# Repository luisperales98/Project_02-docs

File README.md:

# Project_02-docs
PCB design for Golf Ball Dispenser

I apologize for the messiness of the depository... At first I was not able to make subfolders, but then I did it but was not
able to delete the files already uploaded.

This repository shows the PCB design for my Golf Ball Dispenser Project. 
The general function for this device is that it dispenses a golf ball using a Servo motor when motion is detected from the PIR sensor and at the same time plays a little jingle as well. For more information, go to my hackster page below:
https://www.hackster.io/luis-perales/golf-ball-dispenser-301dcc

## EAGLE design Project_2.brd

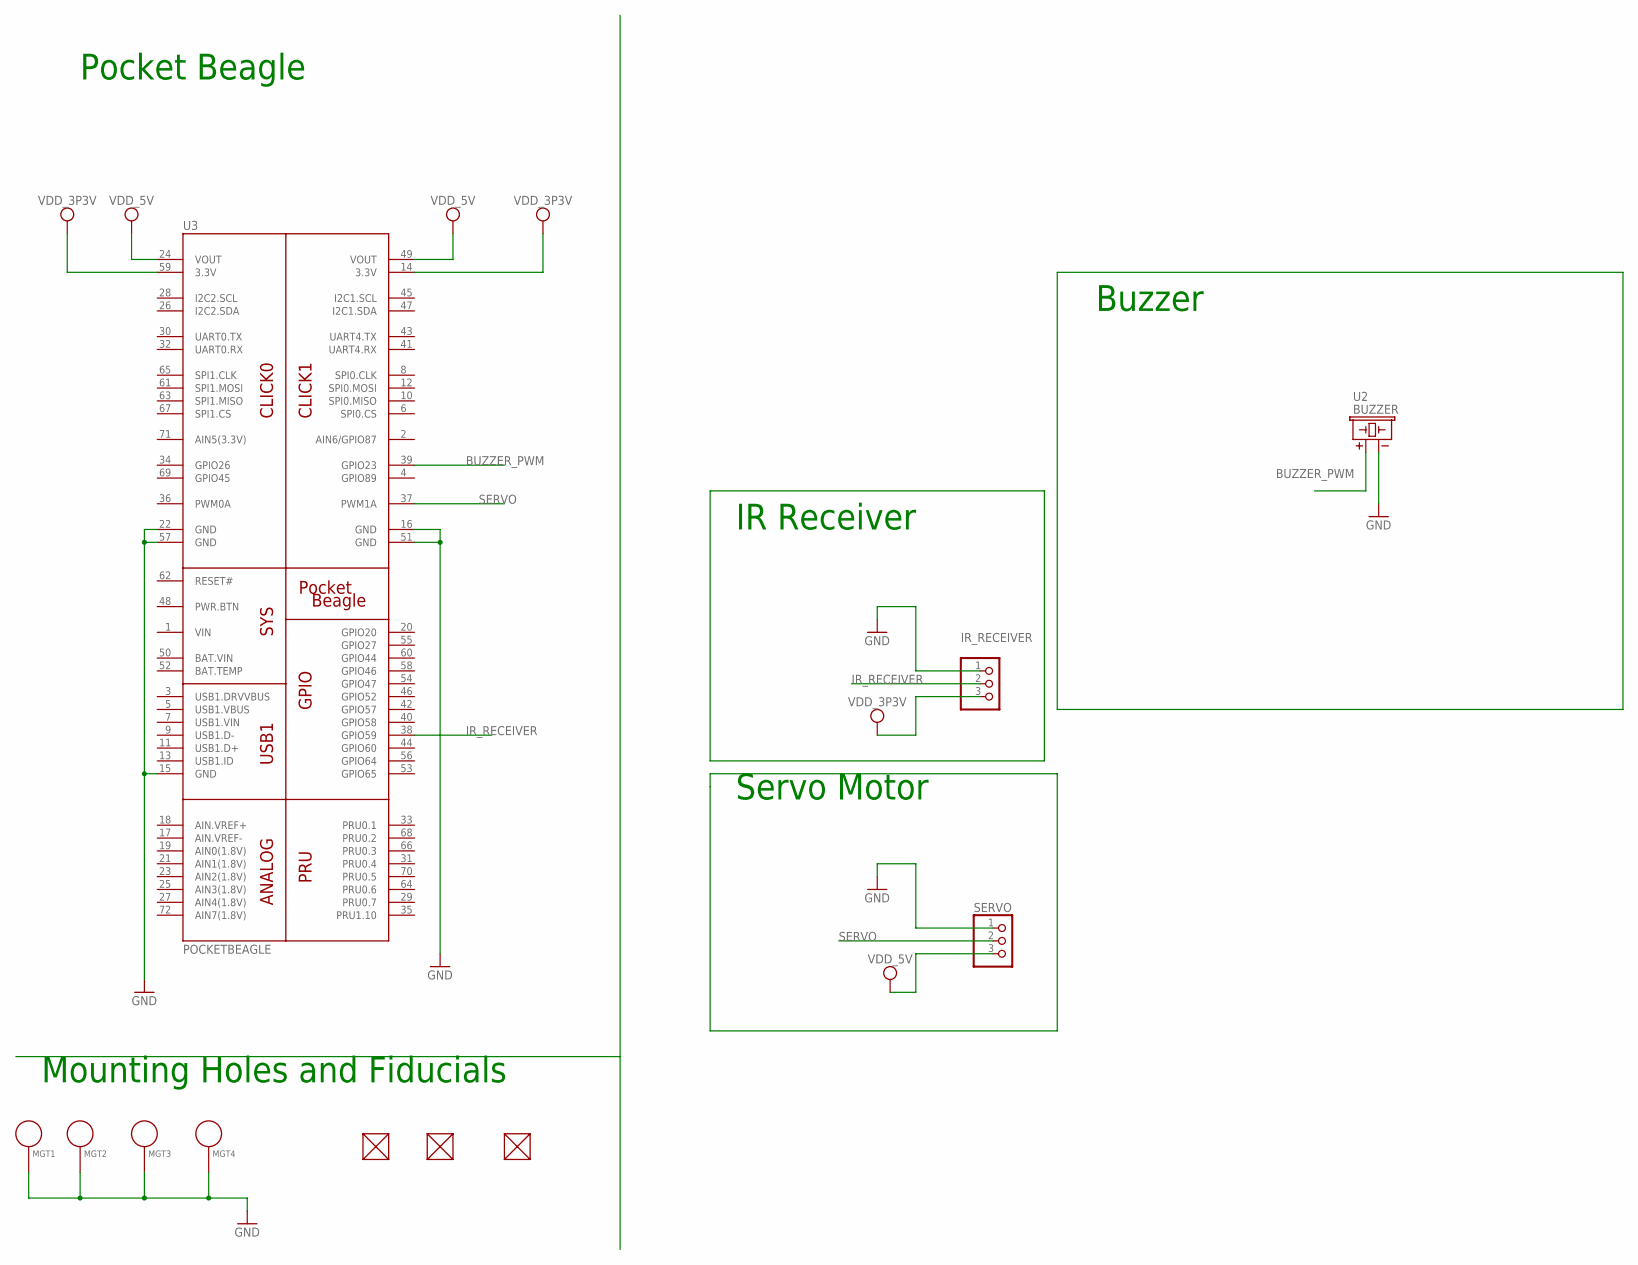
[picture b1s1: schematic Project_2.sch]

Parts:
FUD1, FUD2, FUD3: FIDUCIAL; FIDUCIAL_40MIL
IR_RECEIVER: PINHD-1X3; 1X03
MGT1, MGT2, MGT3, MGT4: MOUNTING_HOLE
SERVO: PINHD-1X3; 1X03
U2: BUZZER; BUZZER_6.5MM
U3: POCKETBEAGLE

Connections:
BAT.VIN: U3.50 (BAT.VIN)
BUZZER_PWM: U2.+, U3.39 (GPIO23)
GND: IR_RECEIVER.1, MGT1.P$1, MGT2.P$1, MGT3.P$1, MGT4.P$1, SERVO.1, U2.-, U3.15 (GND), U3.16 (GND), U3.22 (GND), U3.51 (GND), U3.57 (GND)
IR_RECEIVER: IR_RECEIVER.2, U3.38 (GPIO59)
SERVO: SERVO.2, U3.37 (PWM1A)
VDD_3P3V: IR_RECEIVER.3, U3.14 (3.3V), U3.59 (3.3V)
VDD_5V: SERVO.3, U3.24 (VOUT), U3.49 (VOUT)
VIN: U3.1 (VIN)

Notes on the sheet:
Buzzer
IR Receiver
Servo Motor
Pocket Beagle
Mounting Holes and Fiducials

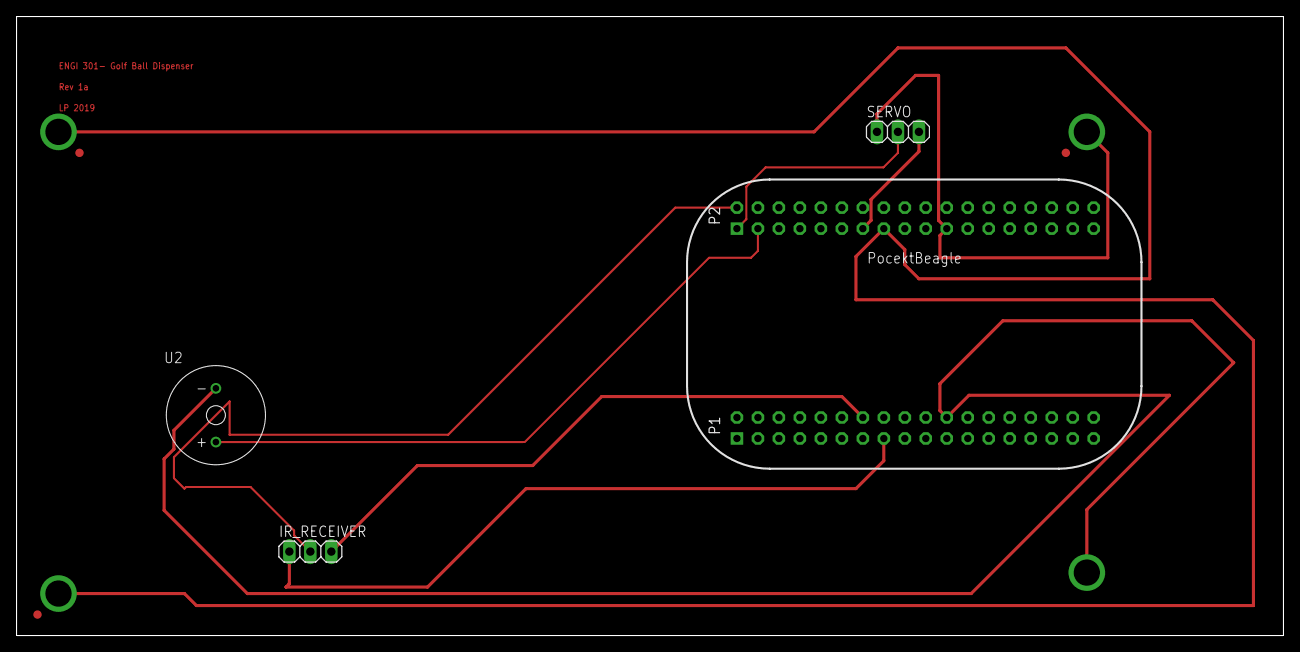
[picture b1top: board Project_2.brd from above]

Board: 2 copper layers, 153.3 x 74.9 mm, 11 parts (0 on the bottom side), 6 nets.

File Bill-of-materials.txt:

Partlist exported from /Users/luisperaels/Documents/EAGLE/projects/Project_2.sch at 12/18/19 5:33 PM

Qty Value         Device        Package        Parts                  Description                                    POPULARITY
2                 PINHD-1X3     1X03           IR_RECEIVER, SERVO     PIN HEADER                                     92        
1   BUZZER        BUZZER        BUZZER_6.5MM   U2                     CEM-1203 Buzzer                                          
3   FIDUCIAL      FIDUCIAL      FIDUCIAL_40MIL FUD1, FUD2, FUD3                                                                
4   MOUNTING_HOLE MOUNTING_HOLE MOUNTING_HOLE  MGT1, MGT2, MGT3, MGT4 Chassis Mounting Hole w/GND connection ability           
1   POCKETBEAGLE  POCKETBEAGLE  POCKETBEAGLE   U3

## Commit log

2019-12-18 Create Eagle
2019-12-18 Create Project_2
2019-12-18 Create N-A
